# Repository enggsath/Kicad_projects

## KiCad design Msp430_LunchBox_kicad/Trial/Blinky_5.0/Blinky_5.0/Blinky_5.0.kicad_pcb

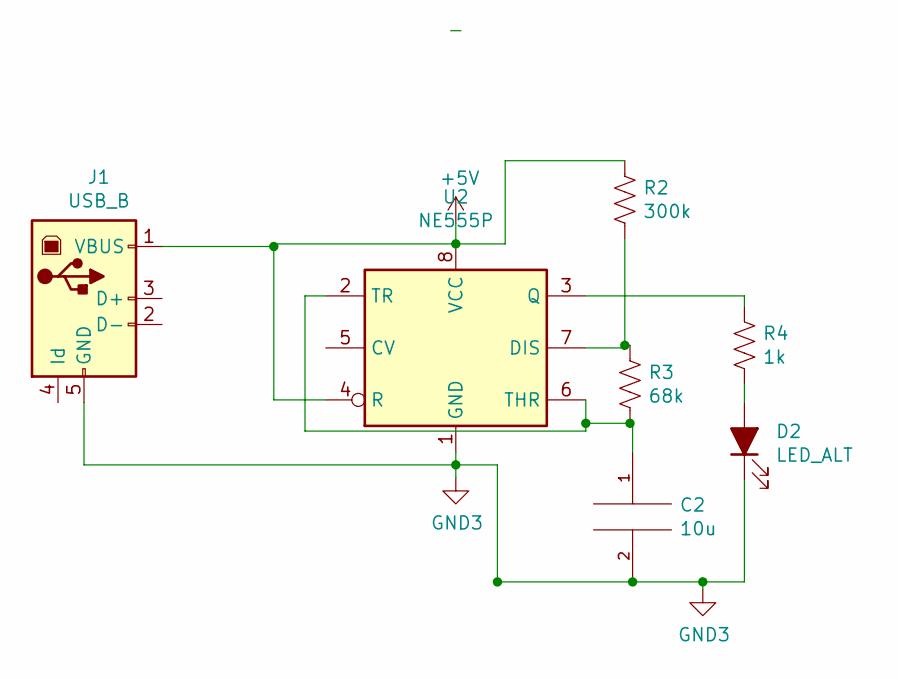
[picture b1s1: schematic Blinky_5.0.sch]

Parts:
C2: 10u; C_0805_2012Metric
D2: LED_ALT; LED_D3.0mm
J1: USB_B; USB_Micro-B_Amphenol_10118194_Horizontal
R2: 300k; R_Axial_DIN0207_L6.3mm_D2.5mm_P10.16mm_Horizontal
R3: 68k; R_Axial_DIN0207_L6.3mm_D2.5mm_P10.16mm_Horizontal
R4: 1k; R_Axial_DIN0207_L6.3mm_D2.5mm_P10.16mm_Horizontal
U2: NE555P; DIP-8_W7.62mm

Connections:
+5V: J1.1 (VBUS), R2.1, U2.4 (R), U2.8 (VCC)
GND3: C2.2, D2.1 (K), J1.5 (GND), U2.1 (GND)
unnamed: C2.1, R3.2, U2.2 (TR), U2.6 (THR)
unnamed: D2.2 (A), R4.2
unnamed: R2.2, R3.1, U2.7 (DIS)
unnamed: R4.1, U2.3 (Q)

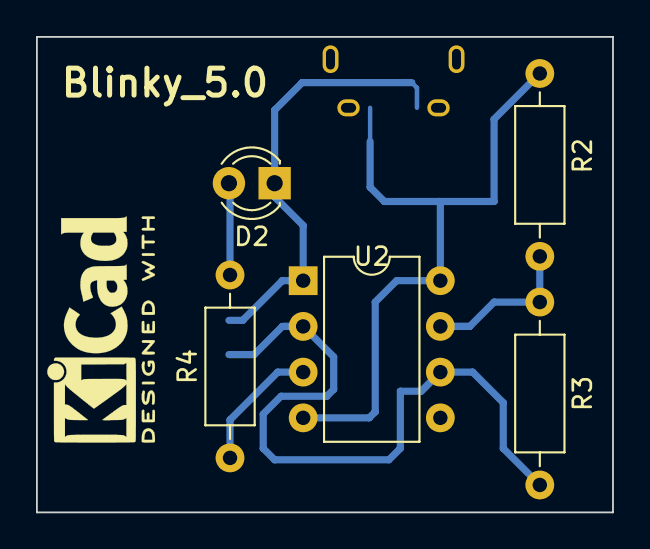
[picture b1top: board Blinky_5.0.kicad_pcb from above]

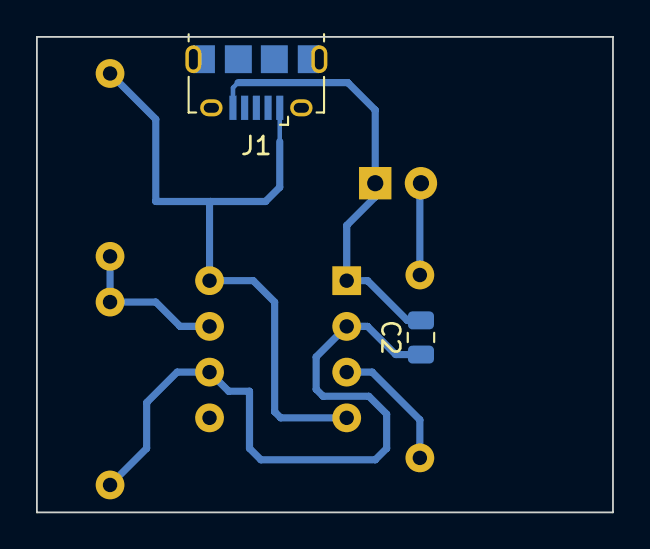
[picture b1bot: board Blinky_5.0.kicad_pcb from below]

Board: 2 copper layers, 32.0 x 26.4 mm, 7 parts (2 on the bottom side), 6 nets.

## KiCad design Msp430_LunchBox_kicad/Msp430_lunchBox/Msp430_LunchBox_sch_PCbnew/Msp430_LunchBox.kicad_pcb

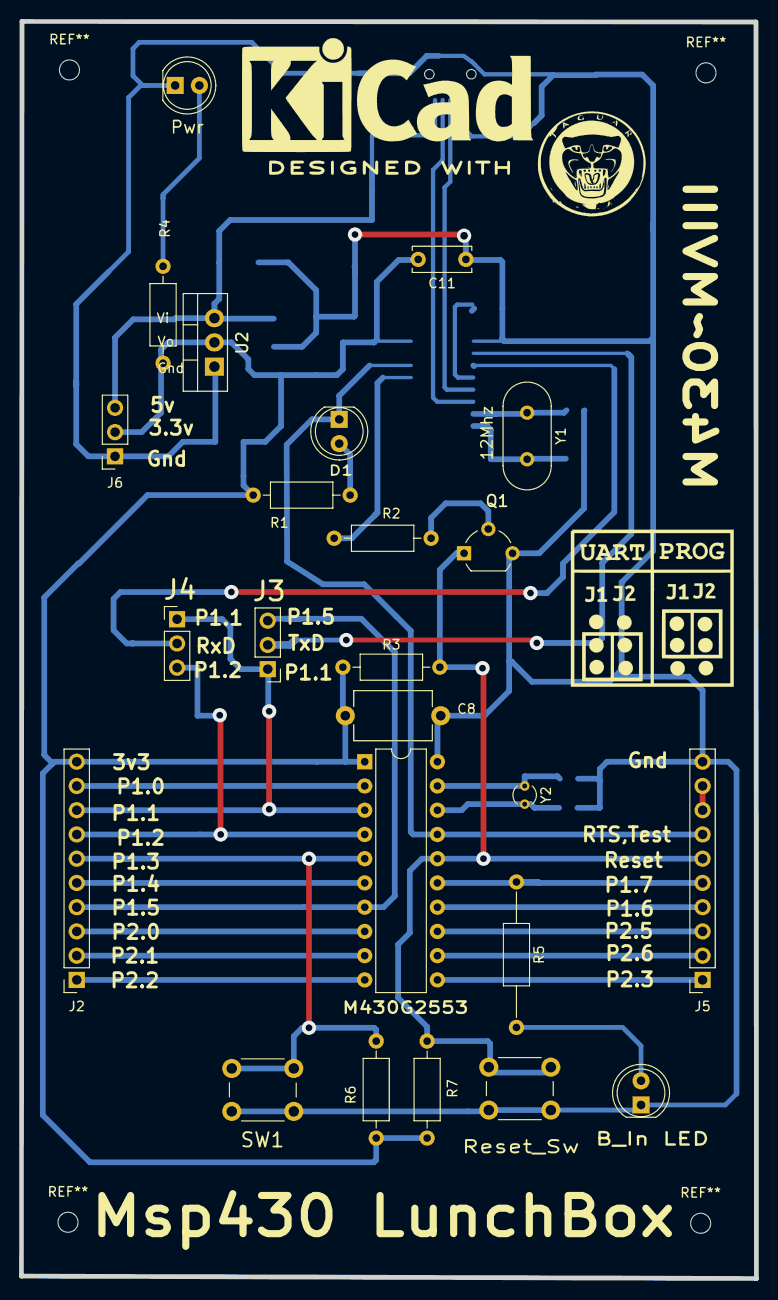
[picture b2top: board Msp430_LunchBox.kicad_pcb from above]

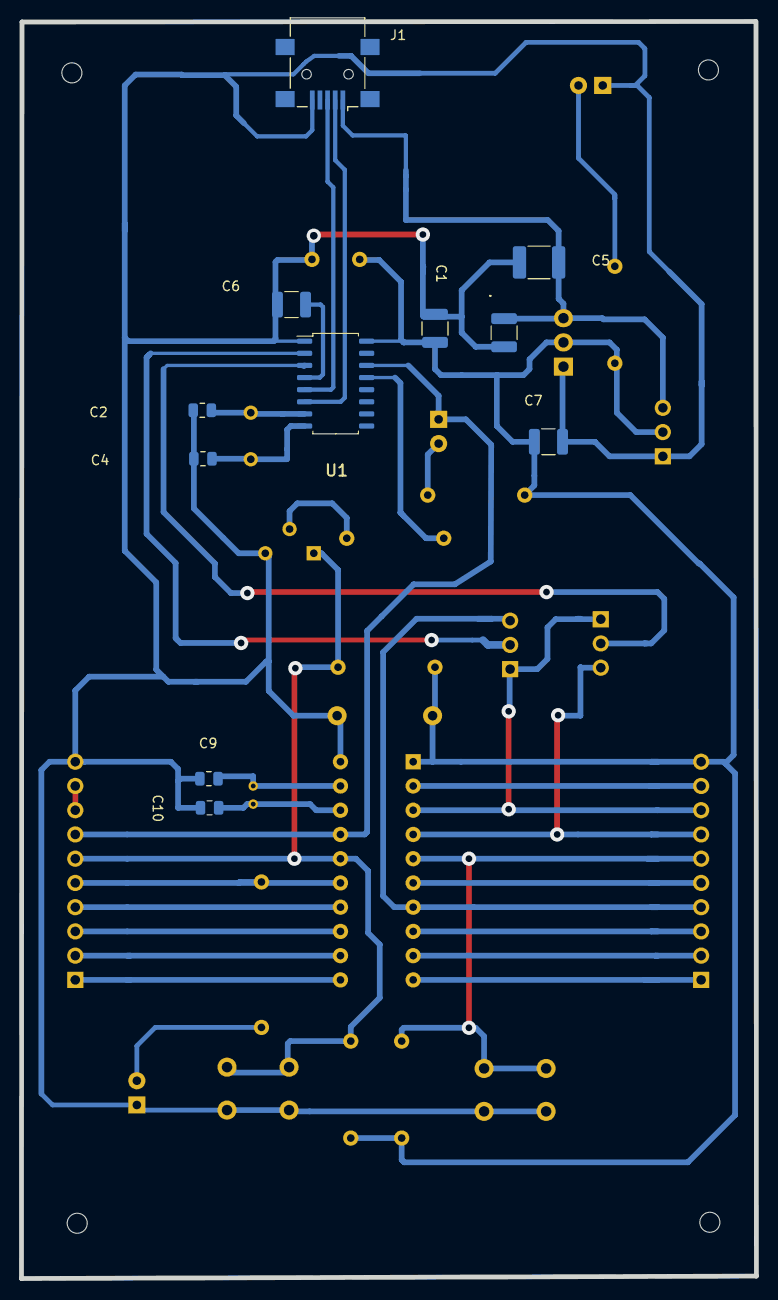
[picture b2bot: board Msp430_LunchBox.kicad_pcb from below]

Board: 2 copper layers, 77.0 x 131.7 mm, 35 parts (11 on the bottom side), 34 nets.

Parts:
 B_In LED: LED; LED_D5.0mm
C1: 0.1u; C_1210_3225Metric
C2, C4, C9, C10: 22pF; C_0805_2012Metric
C3, C6: 0.1uF; C_1210_3225Metric
C5: 10uF; C_1812_4532Metric
C7: 10uF; C_1210_3225Metric
C8: 0.1uF; C_Disc_D8.0mm_W5.0mm_P10.00mm
C11: 0.1uF; C_Disc_D6.0mm_W2.5mm_P5.00mm
D1: LED; LED_D5.0mm
J1: USB_B_Mini; USB_Mini-B_Lumberg_2486_01_Horizontal
J2: Conn_01; PinSocket_1x10_P2.54mm_Vertical
J3: CJ2; PinHeader_1x03_P2.54mm_Vertical
J4: CJ1; PinHeader_1x03_P2.54mm_Vertical
J5: Conn_02; PinSocket_1x10_P2.54mm_Vertical
J6: Power; PinSocket_1x03_P2.54mm_Vertical
M430G2553: MSP430G2553IN20; DIP-20_W7.62mm
Pwr: PWR; LED_D5.0mm
Q1: BC547; TO-92_Wide
R1, R2, R3, R4, R6, R7: 1k; R_Axial_DIN0207_L6.3mm_D2.5mm_P10.16mm_Horizontal
R5: 1k; R_Axial_DIN0207_L6.3mm_D2.5mm_P15.24mm_Horizontal
Reset_Sw: Sw_Reset; SW_PUSH_6mm_H5mm
SW1: Sw_P1.3; SW_PUSH_6mm_H5mm
U1: CH340G; SOIC-16_4.55x10.3mm_P1.27mm
U2: LD1117; TO-220-3_Vertical
Y1: 12Mhz; Crystal_HC49-U_Vertical
Y2: 32.768KHz; Crystal_C26-LF_D2.1mm_L6.5mm_Vertical

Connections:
+3V3: C1.1, C7.1, C8.1, C11.2, J2.10, J6.2, M430G2553.1, R1.1, R3.1, R4.1, R6.2, R7.1, U1.16, U2.2
+5V: C3.1, C5.1, J1.1, J6.3, U2.3
/DTR: R2.2, U1.13
Dm: J1.2, U1.6
Dp: J1.3, U1.5
GND: B_In LED.1, C1.2, C2.2, C3.2, C4.2, C5.2, C6.2, C7.2, C8.2, C9.2, C10.2, C11.1, J1.5, J5.10, J6.1, M430G2553.20, Pwr.1, Q1.3, Reset_Sw.2, SW1.2, U1.1, U2.1
NS15: J5.8, J5.9
unnamed: C2.1, U1.7, Y1.1
unnamed: C4.1, U1.8, Y1.2
unnamed: C6.1, U1.4
unnamed: C9.1, M430G2553.19, Y2.1
unnamed: C10.1, M430G2553.18, Y2.2
unnamed: D1.2, R1.2
unnamed: Pwr.2, R4.2
unnamed: B_In LED.2, R5.2
unnamed: Q1.2, R2.1
P1.0: J2.9, M430G2553.2
P1.1: J2.8, J3.1, J4.1, M430G2553.3
P1.2: J2.7, J4.3, M430G2553.4
P1.3: J2.6, M430G2553.5, R6.1, SW1.1
P1.4: J2.5, M430G2553.6
P1.5: J2.4, J3.3, M430G2553.7
P1.6: J5.4, M430G2553.14
P1.7: J5.5, M430G2553.15, R5.1
P2.0: J2.3, M430G2553.8
P2.1: J2.2, M430G2553.9
P2.2: J2.1, M430G2553.10
P2.3: J5.1, M430G2553.11
P2.4: J5.2, M430G2553.12
P2.5: J5.3, M430G2553.13
RTS,Test: D1.1, J5.7, M430G2553.17, U1.14
Reset: J5.6, M430G2553.16, Q1.1, R3.2, R7.2, Reset_Sw.1
RxD: J4.2, U1.3
TxD: J3.2, U1.2

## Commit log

2021-02-17 Msp430_lunchBox using kicad
2021-06-23 added schematic's and board pdf
